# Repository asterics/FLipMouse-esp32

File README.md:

# FLipMouse goes ESP32

This repository contains the ongoing progress on the firmware for the FLipMouse version 3.
It will be API-compatible with FLipMouse v2, but with major improvements on speed (instead of one CortexM0 we will have a dual-core Tensilica and an additional CortexM0 for USB).

If you want to have a look at the FLipMouse v2, follow [this](https://github.com/asterics/FLipMouse) link to the main repository.

The BLE-HID stuff is based on the other [repository](https://github.com/asterics/esp32_mouse_keyboard), where we use the ESP32 as BLE module replacement.

Online demo version of Web GUI: https://asterics.github.io/FLipMouse-esp32/

__Following 3 steps are necessary to completely update/flash the firmware and the necessary support files/devices:__

## Building the ESP32 firmware

Please follow the step-by-step instructions of Espressif's ESP-IDF manual to setup the build infrastructure:
[Setup Toolchain](https://esp-idf.readthedocs.io/en/latest/get-started/index.html#setup-toolchain)

__Note:__ Due to frequent breaking changes within the esp-idf and all build tools, we recommend to use a specific version of the tools:
* release v4.1 (on 04.02.2020)
* master branch (on 04.02.2020)

To get this version, use the following commands:

  `git clone -b release/v4.1 --recursive https://github.com/espressif/esp-idf.git`  
  `cd esp-idf`  
  `./install.sh`  
  `. ./export.sh`  

																																																																																																																																																																																																																																																																																																																																																																																																																																																																																																																																																																																																																																																																																																																																																																																																																																																																																																																																																																																																																																																																																																																																																																																																																																																																																																																																																																																																																																																																																																																																																																																																																																																																																																																																																																																																																																																																																																																																																																																																																																																																																																																																																																																																												
__Now change your directory into the root directory of this repository.__

Create the sdkconfig:
* Execute `make menuconfig` in this directory
* Change: `Serial flasher config` -> `Flash size` to __4MB__
* Change: `Partition table` -> `Partition table` to __Custom partition table CSV__
* Change: `Component config` -> `Bluetooth` to enabled

Optional (for runtime statistics):
* Change: `Component config`->`FreeRTOS`->`Enable FreeRTOS trace facility` to enabled

Optional (extensive stack/heap debugging):
* Change `Component config`->`Heap memory debugging`->`Heap corruption detection` to whatever you need

After a successful setup, you should be able to build the FLipMouse/FABI firmware by executing 'make flash monitor'.

## Building the LPC11U14 firmware (USB bridging chip)

The dedicated USB chip firmware is located in this repository: [usb_bridge](https://github.com/benjaminaigner/usb_bridge/).
Please clone this repository, and import it into the MCUXpresso IDE.

You can download the IDE here:
[MCUXpresso IDE](http://www.nxp.com/mcuxpresso/ide)

After a successful build, you need to flash the firmware to the LPC11U14 chip. We recommend using a development board by Embedded Artists,
because it is very useful for initial testing & debugging. It is possible to split this board into two pieces, one LPC11U14 target and a JTAG
programmer, which we use on a fully assembled FLipMouse. Please refer to the corresponding documents of this board how to connect the JTAG header to
our FLipMouse (will be announced as soon as the PCB is final).

LPCXpresso development board:

[LPCXpresso 11U14](http://embeddedartists.com/products/lpcxpresso/lpc11U14_xpr.php)

## Uploading the WebGUI

The FLipMouse with ESP32 contains a web interface for customizing the parameters. The web page itself is located in the FAT partition as the config data.

-----------------------

TBA: I think it is very easy to use mkfats by copying the component into ESP-IDF and simply call **make mkfatfs** to build the tool and **make flashfatfs** to upload the image.

**BUT** we have a 8.3 naming convention here...

Currently proposed workflow:

-----------------------

Please clone/download the [mkfats](https://github.com/jkearins/ESP32_mkfatfs) tool, and copy the folder `ESP32_mkfatfs/components/mkfatfs` into your
ESP-IDF's components path.

Execute `make mkfatfs` in this repository to build the *mkfatfs* tool.

If you want to update the webpage on the FLipMouse/FABI device, execute:

`make makefatfs flashfatfs`

_WARNING:_** All your slot configuration and IR commands will be deleted by this operation.

## WARNING: THIS IS EARLY WORK IN PROGRESS

# Acknowledgements

Supporters, MA23, people using this device and many more for input.

ESP-IDF developers for HOG testcode

mkfatfs project

thanks to Luca Dentella for the esp32lights demo, see http://www.lucadentella.it/en/2018/01/08/esp32lights/

thanks to Jeroen Domburg and Cornelis for the captive portal DNS code, see: https://github.com/cornelis-61/esp32_Captdns

thanks to Thomas Barth for esp32 Websocket demo code, see https://github.com/ThomasBarth/WebSockets-on-the-ESP32/

thanks to Lucas Bruder for the Neopixel library for ESP32, see https://github.com/Lucas-Bruder/ESP32_LED_STRIP/

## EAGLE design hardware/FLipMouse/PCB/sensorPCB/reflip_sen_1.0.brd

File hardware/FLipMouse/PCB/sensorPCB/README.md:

# Sensor build-up

This sensor carrier is intended to be used with Velostat material. You need a sheet of Velostat, which matches the PCB size (including all holes).

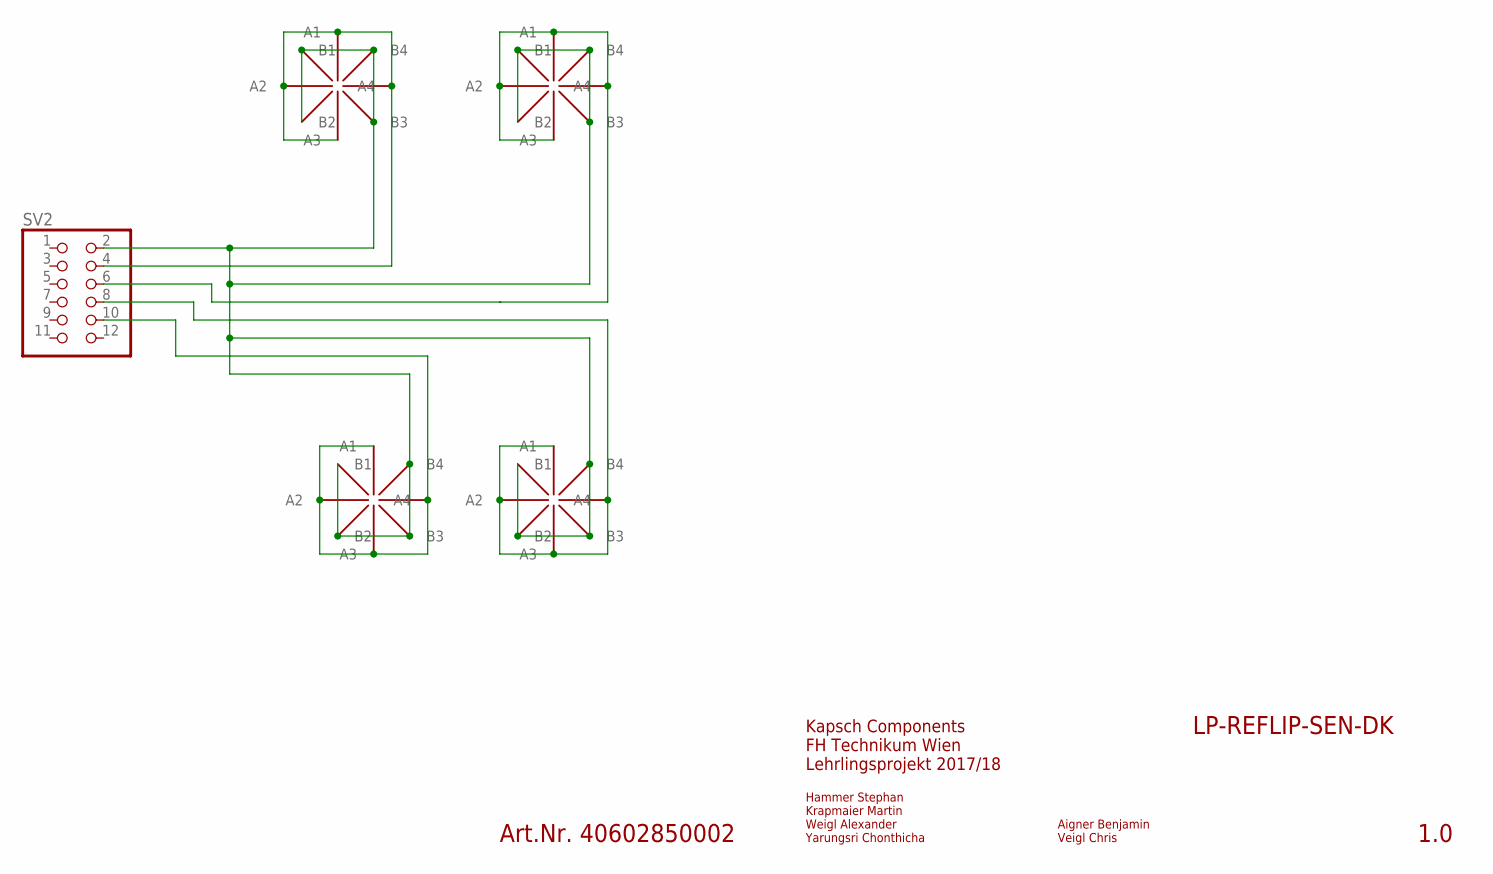
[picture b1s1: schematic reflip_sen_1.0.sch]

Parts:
SV2: PINHD-2X6_2.54-SMD; 2X06SMD
U$1, U$2, U$3, U$4: KONTAKTFLAECHE

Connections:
unnamed: SV2.10, U$2.A1, U$2.A2, U$2.A3, U$2.A4
unnamed: SV2.8, U$4.A1, U$4.A2, U$4.A3, U$4.A4
unnamed: SV2.4, U$1.A1, U$1.A2, U$1.A3, U$1.A4
unnamed: SV2.6, U$3.A1, U$3.A2, U$3.A3, U$3.A4
unnamed: SV2.2, U$1.B1, U$1.B2, U$1.B3, U$1.B4, U$2.B1, U$2.B2, U$2.B3, U$2.B4, U$3.B1, U$3.B2, U$3.B3, U$3.B4, U$4.B1, U$4.B2, U$4.B3, U$4.B4

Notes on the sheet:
Hammer Stephan Krapmaier Martin Weigl Alexander Yarungsri Chonthicha
Kapsch Components FH Technikum Wien Lehrlingsprojekt 2017/18
Art.Nr. 40602850002
Aigner Benjamin Veigl Chris

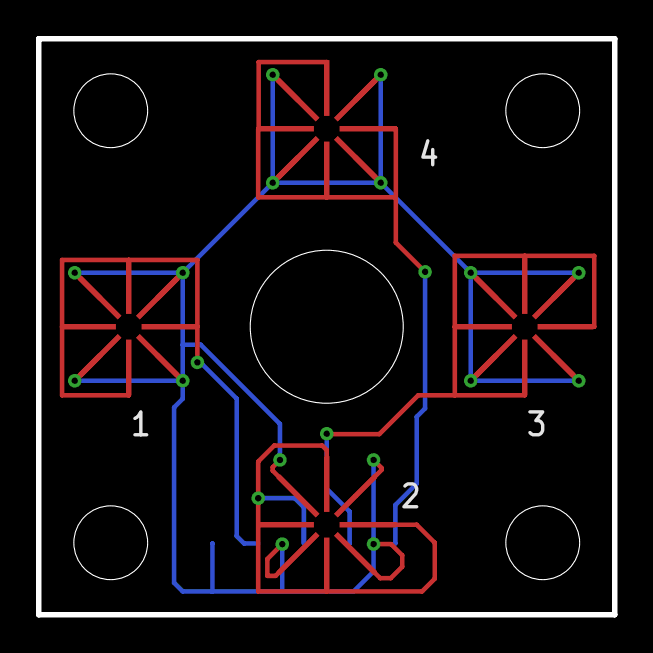
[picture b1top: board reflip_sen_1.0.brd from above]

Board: 2 copper layers, 32.0 x 32.0 mm, 5 parts (1 on the bottom side), 5 nets.

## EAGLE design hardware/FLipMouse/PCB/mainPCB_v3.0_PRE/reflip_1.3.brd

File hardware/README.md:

# FABI

This PCB is intended to be used with a **AK-S-01** case, produced by Szomk.

**Note:** This PCB was not produced yet, so no functional guarantee!

# FLipMouse 

This FLipMouse-esp32 PCB is tested by the *_PRE versions of the PCB.

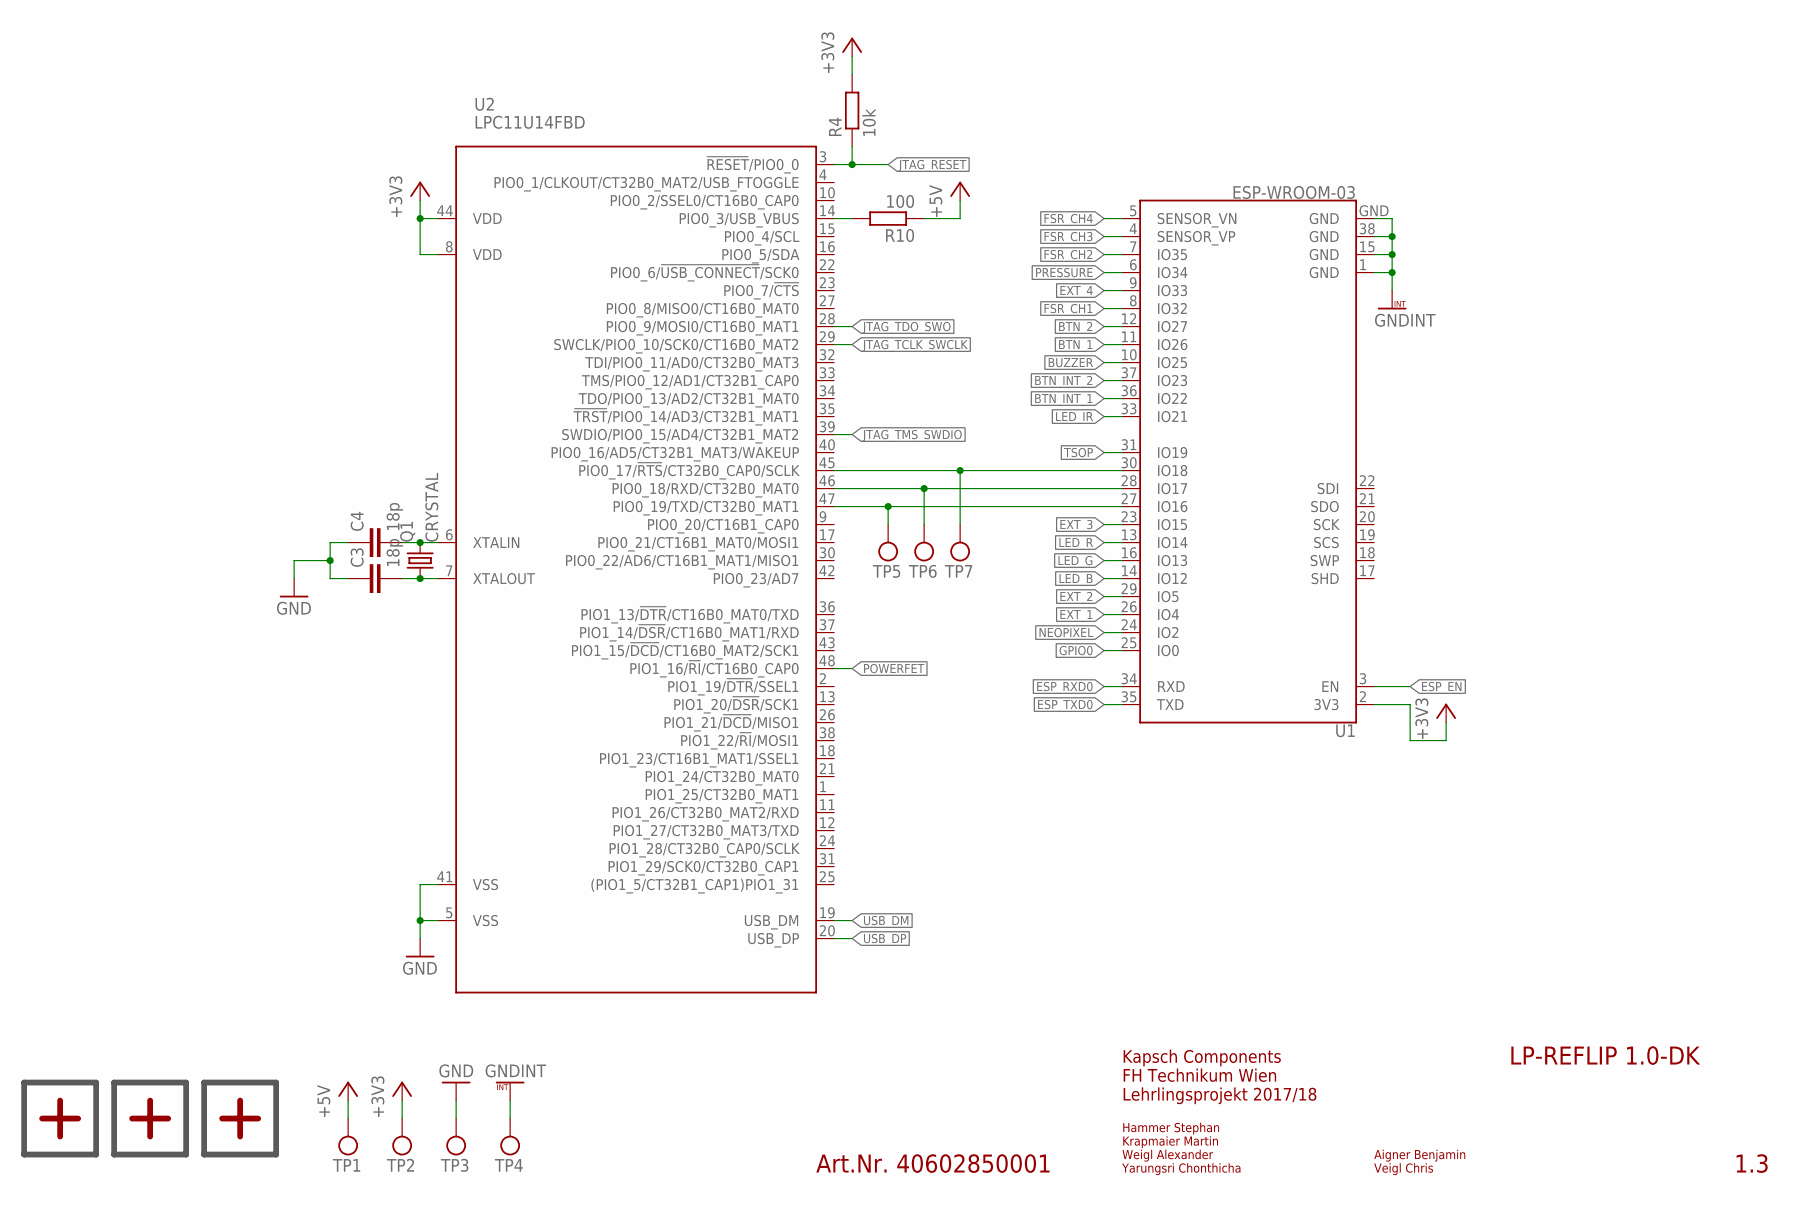
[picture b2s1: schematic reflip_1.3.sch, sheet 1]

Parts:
C3, C4: 18p; C0603
Q1: CRYSTAL
R4: 10k; R0603
R10: 100; R0603
U1: ESP-WROOM-03
U2: LPC11U14FBD; SOT313-2
U$3, U$4, U$5: PASSMARKE
U$6: TP1; TESTPUNKT
U$7: TP2; TESTPUNKT
U$8: TP3; TESTPUNKT
U$9: TP4; TESTPUNKT
U$10: TP7; TESTPUNKT
U$11: TP6; TESTPUNKT
U$12: TP5; TESTPUNKT

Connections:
+3V3: R4.2, U1.2 (3V3), U2.8 (VDD), U2.44 (VDD), U$7.P$1; also elsewhere on the board
+5V: R10.1, U$6.P$1; also elsewhere on the board
BTN_1: U1.11 (IO26); also elsewhere on the board
BTN_2: U1.12 (IO27); also elsewhere on the board
BTN_INT_1: U1.36 (IO22); also elsewhere on the board
BTN_INT_2: U1.37 (IO23); also elsewhere on the board
BUZZER: U1.10 (IO25); also elsewhere on the board
ESP_EN: U1.3 (EN); also elsewhere on the board
ESP_RXD0: U1.34 (RXD); also elsewhere on the board
ESP_TXD0: U1.35 (TXD); also elsewhere on the board
EXT_1: U1.26 (IO4); also elsewhere on the board
EXT_2: U1.29 (IO5); also elsewhere on the board
EXT_3: U1.23 (IO15); also elsewhere on the board
EXT_4: U1.9 (IO33); also elsewhere on the board
FSR_CH1: U1.8 (IO32); also elsewhere on the board
FSR_CH2: U1.7 (IO35); also elsewhere on the board
FSR_CH3: U1.4 (SENSOR_VP); also elsewhere on the board
FSR_CH4: U1.5 (SENSOR_VN); also elsewhere on the board
GND: C3.1, C4.1, U2.5 (VSS), U2.41 (VSS), U$8.P$1; also elsewhere on the board
GNDINT: U1.1 (GND), U1.15 (GND), U1.38 (GND), U1.GND, U$9.P$1; also elsewhere on the board
GPIO0: U1.25 (IO0); also elsewhere on the board
JTAG_RESET: R4.1, U2.3 (!RESET!/PIO0_0); also elsewhere on the board
JTAG_TCLK_SWCLK: U2.29 (SWCLK/PIO0_10/SCK0/CT16B0_MAT2); also elsewhere on the board
JTAG_TDO_SWO: U2.28 (PIO0_9/MOSI0/CT16B0_MAT1); also elsewhere on the board
JTAG_TMS_SWDIO: U2.39 (SWDIO/PIO0_15/AD4/CT32B1_MAT2); also elsewhere on the board
LED_B: U1.14 (IO12); also elsewhere on the board
LED_G: U1.16 (IO13); also elsewhere on the board
LED_IR: U1.33 (IO21); also elsewhere on the board
LED_R: U1.13 (IO14); also elsewhere on the board
LPC_RXD: U1.28 (IO17), U2.46 (PIO0_18/RXD/CT32B0_MAT0), U$11.P$1
LPC_SIG: U1.30 (IO18), U2.45 (PIO0_17/!RTS!/CT32B0_CAP0/SCLK), U$10.P$1
LPC_TXD: U1.27 (IO16), U2.47 (PIO0_19/TXD/CT32B0_MAT1), U$12.P$1
unnamed: C4.2, Q1.P$2 (2), U2.6 (XTALIN)
unnamed: R10.2, U2.14 (PIO0_3/USB_VBUS)
unnamed: C3.2, Q1.P$1 (1), U2.7 (XTALOUT)
NEOPIXEL: U1.24 (IO2); also elsewhere on the board
POWERFET: U2.48 (PIO1_16/!RI!/CT16B0_CAP0); also elsewhere on the board
PRESSURE: U1.6 (IO34); also elsewhere on the board
TSOP: U1.31 (IO19); also elsewhere on the board
USB_DM: U2.19 (USB_DM); also elsewhere on the board
USB_DP: U2.20 (USB_DP); also elsewhere on the board

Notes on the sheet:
Hammer Stephan Krapmaier Martin Weigl Alexander Yarungsri Chonthicha
Kapsch Components FH Technikum Wien Lehrlingsprojekt 2017/18
Aigner Benjamin Veigl Chris
Art.Nr. 40602850001

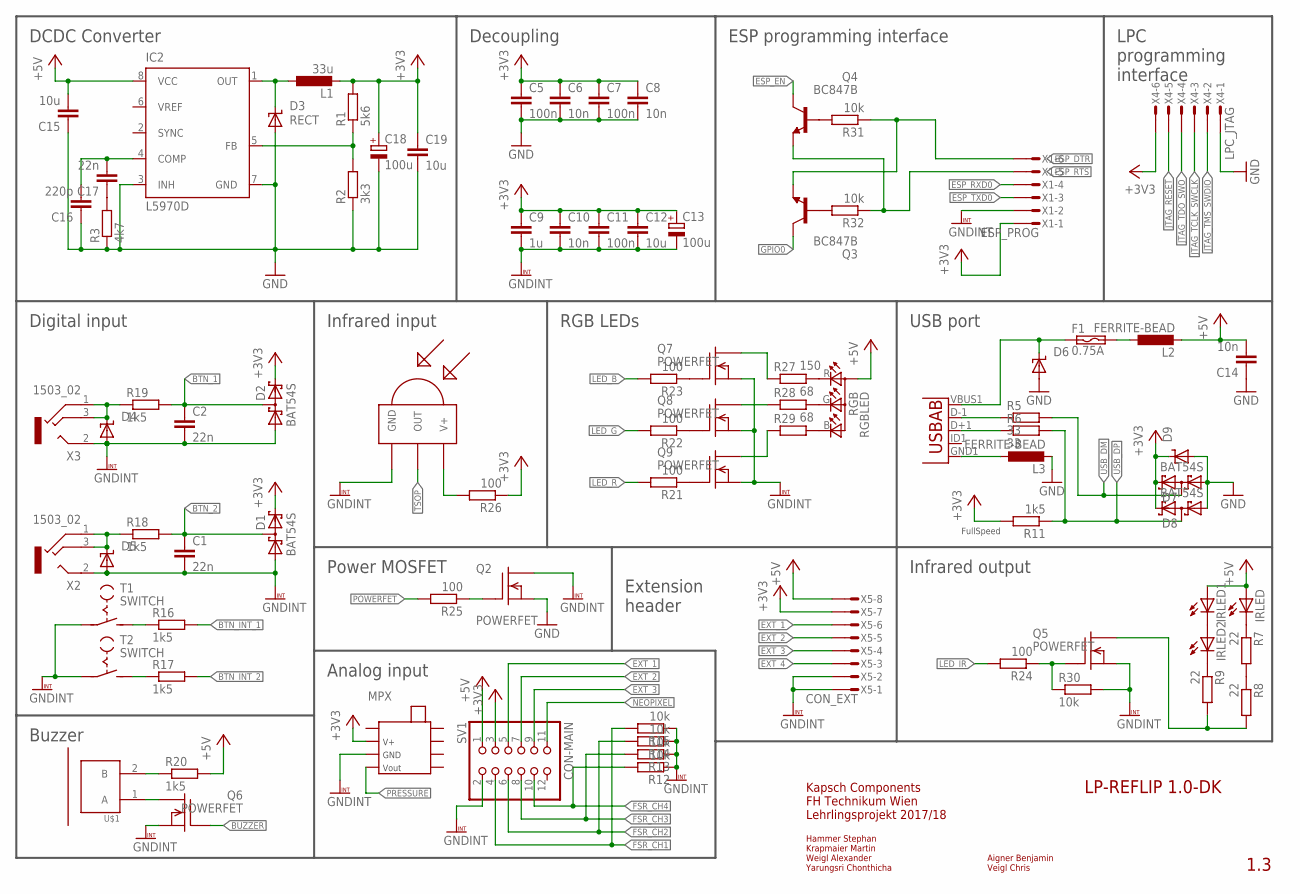
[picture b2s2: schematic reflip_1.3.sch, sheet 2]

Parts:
C1, C2, C17: 22n; C0603
C5, C7, C11: 100n; C0603
C6, C8, C10, C14: 10n; C0603
C9: 1u; C0603
C12, C15, C19: 10u; C0603
C13, C18: 100u; PANASONIC_D
C16: 220p; C0603
D1, D2, D7, D8: BAT54S; SOT23
D3: RECT; SMBJ
D4, D5, D6, D9: TVS-DIODE; SMBJ
F1: 0.75A; FUSE
IC2: L5970D; HSOP8
IRLED, IRLED1, IRLED2: IRLED
L1: 33u; SPULE
L2, L3: FERRITE-BEAD; FERRITEBEAD
MPX: MPX_PRESSURE_SENSOR
Q2, Q5, Q6, Q7, Q8, Q9: POWERFET; SOT-23
Q3, Q4: BC847B; SOT23
R1: 5k6; R0603
R2: 3k3; R0603
R3: 4k7; R0603
R5, R6: 33; R0603
R7, R8, R9: 22; R1206
R11, R16, R17, R18, R19, R20: 1k5; R0603
R12, R13, R14, R15, R30, R31, R32: 10k; R0603
R21, R22, R23, R24, R25, R26: 100; R0603
R27: 150; R0603
R28, R29: 68; R0603
RGB: RGBLED
SV1: CON-MAIN; FE06-2W
T1, T2: SWITCH; SWITCHES
U3: USB""; USB-MICRO-SMD
U$1: PKLCS1212E2400-R1; BUZZ_PIEZO_SMD
U$2: TSOP4838; TSOP18XX
X1: ESP_PROG; MICROMATCH-6SMD
X2, X3: 1503_02
X4: LPC_JTAG; MICROMATCH-6SMD
X5: CON_EXT; MICROMATCH-8-SMD

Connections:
+3V3: C5.1, C6.1, C7.1, C8.1, C9.1, C10.1, C11.1, C12.1, C13.+, C18.+, C19.1, D1.2 (C2), D2.2 (C2), D7.2 (C2), D8.2 (C2), D9.C, L1.P$2 (2), MPX.P$2 (V+), R1.2, R11.2, R26.1, SV1.3, X1.1, X4.6, X5.7; also elsewhere on the board
+5V: C14.2, C15.2, IC2.8 (VCC), IRLED.A, IRLED1.A, L2.P$2 (2), R20.2, RGB.CA (A2), SV1.1, X5.8; also elsewhere on the board
BTN_1: C2.1, D2.3 (C1A2), R19.2; also elsewhere on the board
BTN_2: C1.1, D1.3 (C1A2), R18.2; also elsewhere on the board
BTN_INT_1: R16.2; also elsewhere on the board
BTN_INT_2: R17.2; also elsewhere on the board
BUZZER: Q6.1 (G); also elsewhere on the board
ESP_DTR: Q3.2 (E), R31.1, X1.6
ESP_EN: Q4.3 (C); also elsewhere on the board
ESP_RTS: Q4.2 (E), R32.1, X1.5
ESP_RXD0: X1.4; also elsewhere on the board
ESP_TXD0: X1.3; also elsewhere on the board
EXT_1: SV1.5, X5.6; also elsewhere on the board
EXT_2: SV1.7, X5.5; also elsewhere on the board
EXT_3: SV1.9, X5.4; also elsewhere on the board
EXT_4: X5.3; also elsewhere on the board
FSR_CH1: R15.2, SV1.4; also elsewhere on the board
FSR_CH2: R14.2, SV1.6; also elsewhere on the board
FSR_CH3: R13.2, SV1.8; also elsewhere on the board
FSR_CH4: R12.2, SV1.10; also elsewhere on the board
GND: C5.2, C6.2, C7.2, C8.2, C14.1, C15.1, C16.1, C18.-, C19.2, D3.A, D6.A, D7.1 (A1), D8.1 (A1), D9.A, IC2.3 (INH), IC2.7 (GND), L3.P$2 (2), Q2.2 (S), R2.1, R3.1, X4.1; also elsewhere on the board
GNDINT: C1.2, C2.2, C9.2, C10.2, C11.2, C12.2, C13.-, D1.1 (A1), D2.1 (A1), D4.A, D5.A, MPX.P$3 (GND), Q2.3 (D), Q5.2 (S), Q6.2 (S), Q7.2 (S), Q8.2 (S), Q9.2 (S), R12.1, R13.1, R14.1, R15.1, R30.2, SV1.2, T1.P$3, T2.P$3, U$2.GND, X1.2, X2.2, X3.2, X5.1, X5.2; also elsewhere on the board
GPIO0: Q3.3 (C); also elsewhere on the board
JTAG_RESET: X4.5; also elsewhere on the board
JTAG_TCLK_SWCLK: X4.3; also elsewhere on the board
JTAG_TDO_SWO: X4.4; also elsewhere on the board
JTAG_TMS_SWDIO: X4.2; also elsewhere on the board
LED_B: R23.2; also elsewhere on the board
LED_G: R22.2; also elsewhere on the board
LED_IR: R24.2; also elsewhere on the board
LED_R: R21.2; also elsewhere on the board
unnamed: IC2.5 (FB), R1.1, R2.2
unnamed: Q9.1 (G), R21.1
unnamed: D3.C, IC2.1 (OUT), L1.P$1 (1)
unnamed: R6.1, U3.D+1 (D+)
unnamed: Q2.1 (G), R25.1
unnamed: R5.1, U3.D-1 (D-)
unnamed: C17.1, R3.2
unnamed: IRLED1.C, IRLED2.A
unnamed: C16.2, C17.2, IC2.4 (COMP)
unnamed: Q8.1 (G), R22.1
unnamed: Q7.1 (G), R23.1
unnamed: Q7.3 (D), R27.1
unnamed: IRLED2.C, R9.1
unnamed: R7.2, R8.1
unnamed: R27.2, RGB.R (CRED)
unnamed: D6.C, F1.P$1 (1), U3.VBUS1 (VBUS)
unnamed: F1.P$2 (2), L2.P$1 (1)
unnamed: R17.1, T2.P$4 (S)
unnamed: R20.1, U$1.2 (B)
unnamed: D5.C, R18.1, X2.1, X2.3
unnamed: Q5.3 (D), R8.2, R9.2
unnamed: D4.C, R19.1, X3.1, X3.3
unnamed: Q6.3 (D), U$1.1 (A)
unnamed: R28.2, RGB.G (CGREEN)
unnamed: R26.2, U$2.VCC (V+)
unnamed: L3.P$1 (1), U3.GND1 (GND)
unnamed: R29.2, RGB.B (CBLUE)
unnamed: Q9.3 (D), R29.1
unnamed: Q8.3 (D), R28.1
unnamed: Q5.1 (G), R24.1, R30.1
unnamed: IRLED.C, R7.1
unnamed: Q4.1 (B), R31.2
unnamed: Q3.1 (B), R32.2
NEOPIXEL: SV1.11; also elsewhere on the board
POWERFET: R25.2; also elsewhere on the board
PRESSURE: MPX.P$4 (VOUT); also elsewhere on the board
T1: R16.1, T1.P$4 (S)
TSOP: U$2.OUT; also elsewhere on the board
USB_DM: D7.3 (C1A2), R5.2; also elsewhere on the board
USB_DP: D8.3 (C1A2), R6.2, R11.1; also elsewhere on the board

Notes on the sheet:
DCDC Converter
Decoupling
ESP programming interface
LPC programming interface
Digital input
Infrared input
RGB LEDs
Buzzer
Extension header
Power MOSFET
USB port
Infrared output
FullSpeed
Hammer Stephan Krapmaier Martin Weigl Alexander Yarungsri Chonthicha
Kapsch Components FH Technikum Wien Lehrlingsprojekt 2017/18
Aigner Benjamin Veigl Chris
Analog input

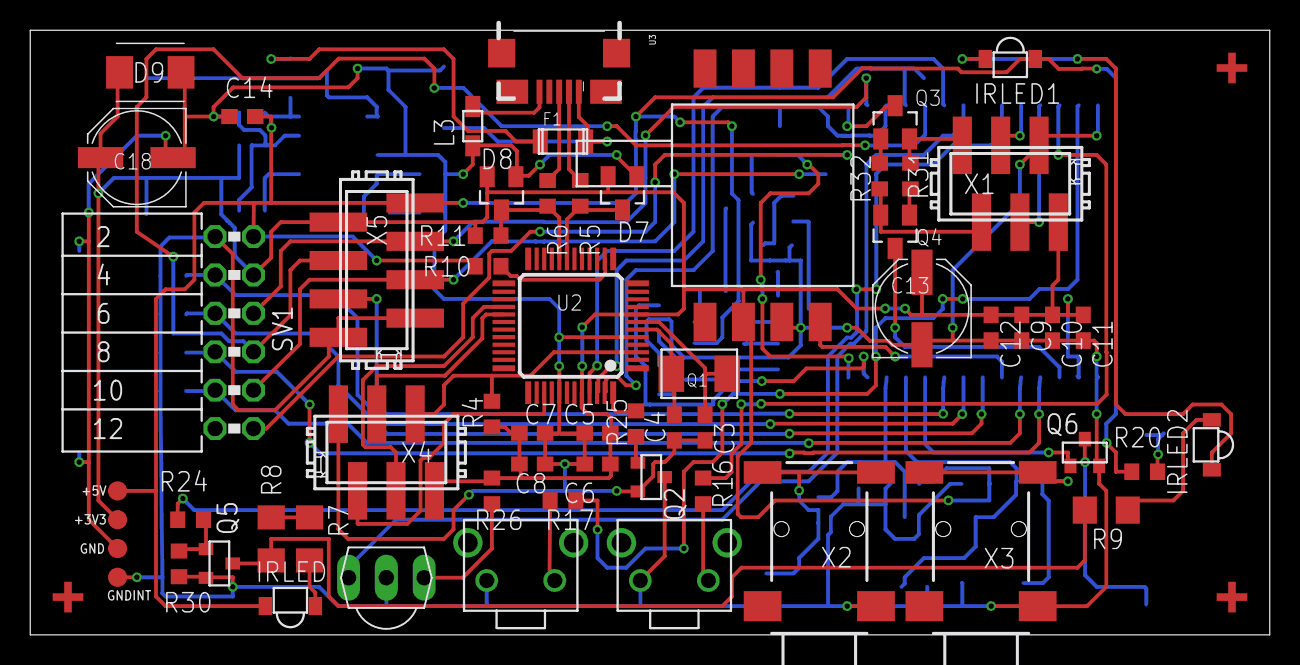
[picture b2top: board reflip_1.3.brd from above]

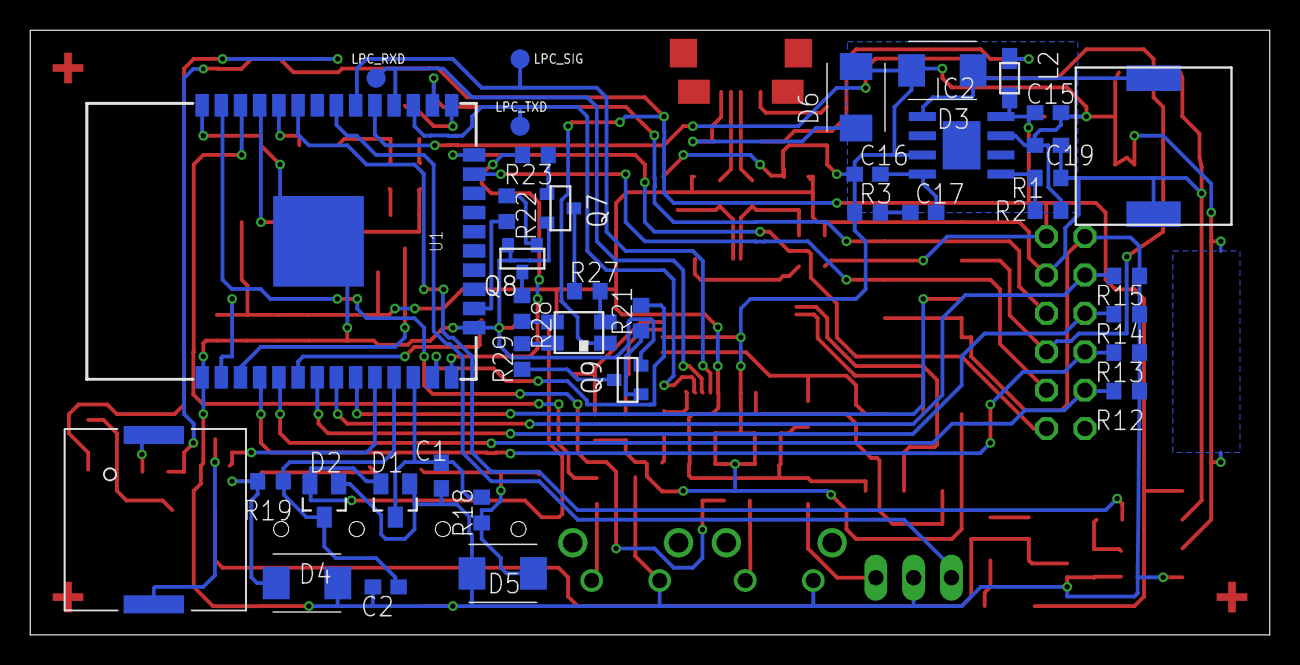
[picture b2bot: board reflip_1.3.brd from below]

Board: 2 copper layers, 82.0 x 40.0 mm, 102 parts (39 on the bottom side), 77 nets.

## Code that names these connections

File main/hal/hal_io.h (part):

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#define HAL_IO_PIN_BUTTON_INT1  5
/** @brief PIN - GPIO pin for internal button 2 (FLipMouse) */
#define HAL_IO_PIN_BUTTON_INT2  14
/** @brief PIN - GPIO pin for buzzer (FLipMouse)
 * @note We will use ledc drivers for the buzzer*/
#define HAL_IO_PIN_BUZZER       25
/** @brief PIN - GPIO pin for IR receiver (TSOP) (FLipMouse) 
 * @note IR will be done with the RMT driver*/
#define HAL_IO_PIN_IR_RECV      12
/** @brief PIN - GPIO pin for IR sender (IR-LED) (FLipMouse)
 * @note IR will be done with the RMT driver */
#define HAL_IO_PIN_IR_SEND      21
/**@brief PIN - GPIO pin for Neopixel onboard LED (&maybe future front LED) */
#define HAL_IO_PIN_NEOPIXEL     22
/** @brief PIN - GPIO pin for external modules */
#define HAL_IO_PIN_EXT          2
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#define HAL_IO_PIN_BUTTON_EXT7  14
/** @brief PIN - GPIO pin for internal button 1 (FABI) */
#define HAL_IO_PIN_BUTTON_INT1  23
/** @brief PIN - GPIO pin for buzzer (FABI)
 * @note We will use ledc drivers for the buzzer*/
#define HAL_IO_PIN_BUZZER       27
/** @brief PIN - GPIO pin for IR receiver (TSOP) (FABI) 
 * @note IR will be done with the RMT driver*/
#define HAL_IO_PIN_IR_RECV      35
/** @brief PIN - GPIO pin for IR sender (IR-LED) (FABI)
 * @note IR will be done with the RMT driver */
#define HAL_IO_PIN_IR_SEND      19
/**@brief PIN - GPIO pin for Neopixel onboard LED */
#define HAL_IO_PIN_NEOPIXEL     22

#endif /* DEVICE_FABI */
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
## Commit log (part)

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2018-05-03 changed colors in order to meet aria contrast criteria
2018-05-03 added translations for "connected" and "not connected"
2018-05-03 added classes for displaying items only for screenreaders and for connection indicators
2018-05-04 changed access keys of sip/puff sliders because alt+e is chrome menu
2018-05-06 Added mode for strong sip/puff
2018-05-06 Added conditions for strong mode + XX in tasks, handling tbd
2018-05-09 Reduced priority of tasks for kbd/mouse/joystick & set baudrate to 115200
2018-05-12 Added a check for current BT status, avoiding errors on re-enabling
2018-05-12 Added compatibility flag
2018-05-12 Starting with slot number 0, not having a "special", not removable slot.
2018-05-12 Added v2.5. note on AT LA/ AT DE
2018-05-12 Put LED update into the macro instead of a task (Neopixel still need a task)
2018-05-16 Fixed heap corruption with reduced buffers
2018-05-21 Changed task priority of config switcher, removed NL characters from ID string
2018-05-21 Added opening partition, to be save if webgui is initialized before storage
2018-05-21 Starting with slot 0, no "DEFAULT" slot
2018-05-21 Changed RMT blocks to 3, on all occasions, freeing one for Neopixels and one for HID output
2018-05-22 Added declaration for queue & usb command
2018-05-23 Added note on slot 0
2018-05-23 Changed for new HID sending
2018-05-23 Added "END" after sending a slot
2018-05-23 Changed storage for slot 0 and -1 for delete all, added note. AT LA bugfix, sending "END" at the end
2018-05-24 Updated documentation & changed loglevel for USB mouse to DEBUG
2018-05-24 Fixed corrupted slots on save due to not-synchronized config data
2018-05-24 Extended data output for saving slots (deactivated by #if 0)
2018-05-28 Removed espressif BLE stuff, added Nkolban's BLE stack
2018-05-28 Improved&simplified calibration:
    - Using same adc read function
    - Removing problem with sensor gain (was not take into account for calibration)
2018-05-28 implemented queue parsing
2018-05-28 BLE/WiFi switch without pairing (is normally active if no device is connected)
2018-05-28 Changed AT BM numbering
2018-05-29 Added sip/puff calibration. Sometimes the 5V type has a significant offset, is calibrated now
2018-05-29 Reduced debug output, controllable via LOG_LEVEL_STORAGE define
2018-05-29 Moved radio switch to main task, reducing stack load on timer
2018-05-29 Reduced main stack size, fixed error on switching off wifi
2018-05-30 Changed stacksize to 8k, replaced printf by ESP_LOGx
2018-05-30 Activated BT/Wifi coexistance, don't know if it helps...
2018-06-04 Changed error checks for getting wifi station count, added guards for wifi deinit
2018-06-04 Doxygen docs updated to current status
2018-06-13 Changed individual tasks to task_hid
2018-06-13 Added HID task
2018-06-13 Added store/load for HID command chain
2018-06-13 Rewrote parser for short HID commands
2018-06-21 Removed now unused kbd/mouse tasks -> moved to task_hid
2018-06-21 Changed comments -> HID task is continous, not functional.
2018-06-21 Changed further to use simple VB task
2018-07-24 Changed sdkconfig & websocket file for esp-idf release v3.1
2018-08-03 Renamed default file to flip.set (allowing a default fabi.set)
2018-08-06 Changed load function to use AT commands from files.
2018-08-07 Major improvements/fixes:
    - Fixed AT AY command
    - Fixing buffer errors on AT SS/AT SP
    - Moved slot storing to an individual function (refactored old printAll function -> now storing AT commands in flash)
    - Slot printing is now mostly done in hal_storage (because the output of "AT LA" is already stored in flash)
2018-08-07 Major improvements:
    - Added a stripping function to remove \r\n
    - Changed config names from 000.fms to 000.set
    - Added serial output to halStorageLoadNumber -> replacing the printAll function from task_commands
    - Added a global file handle for a session, allow appending lines on each call of halStorageStore (less memory for saving AT command lines)
    - Removed all VB/HID chain store/load functions
2018-08-07 Implemented "AT NE" by sending command chain parameter to config switcher queue
2018-08-07 Added breaks for command type detection
2018-08-13 DOXY: Typos, Todos
2018-08-14 OTF calibration, not activated now (missing good values from normal sensors)
2018-10-10 Changed component names for having all part types in one order. Added 3d shapes & beautified silkscreen layers.
2018-10-15 Added requirementsspecification for FABI3 (necessary for certification)
2018-11-15 Production ready, alpha: * Added marks/logos/fiducials * Changed neopixel driving * Moved RX/TX of EXT header from internal UART to free pins * Renumbered all parts for having same part types with fo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
2018-11-21 Checklist: removed EdgeCut layer from single page PCB print Added the update of the 3D renderings
2018-11-21 Improvements&fixes: * Replaced PJ320D (china jack plugs) with plugs from digikey (RoHS!) * Added remaining 3D shapes to PCB * Removed GND from unused jack plug pins (might result in unusable buttons 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
2018-11-25 Pin config update for FABI, removed OTF calibration via defines for FABI
2018-11-25 Added kicad backup files to gitignore, added FABI rescue lib
2018-12-02 Updated FLipMouse PCB: - Routed ADC inputs (FSR+pressure) to LPC11 too (in case of crappy ESP ADC values) - Added ESP32 auto-reset pins to LPC11 (enabling programming via LPC USB) - Cleanup regarding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
2019-01-07 Added function to check if 'sip and puff' is available
2019-01-29 Added default files for FLipMouse configs. Removed gain settings
2019-01-29 Small documentation updates. Fixed R10, according to batch documentation (batch 'a'), from 1k5 to 15R (series resistor for buzzer)
2019-02-05 Clearing empty command queue flag before loading slots. Changed debug level to info
2019-02-05 Changed to use new parser:
    -) Commands are defined now in structure
    -) Parser is based on: https://gitlab.com/ba.1150/cmd_parser_esp32
    -) Parser modifies either the generalConfig_t struct OR calls a handler
2019-02-05 Changed LED number if WiFi is active (now it is purple)
2019-02-05 Added debug output for command chain.
2019-02-05 remove newline
2019-02-06 Keycode parser using parameter, not full string. Added debug output for press action.
2019-02-07 Changed version string to v2.7 (compatible with FlipMouseGUI)
2019-02-08 Updated sdkconfig to esp idf release v3.2
2019-02-08 Changed wifi/ble switching: -) BLE is always active -) BLE/Wifi co-existance is done in esp-idf -) Wifi is switched on/off by the special button handler
2019-02-09 Added detailed debouncer output; added printf macros for printing single bits
2019-02-09 Replaced the out event flags (signalling to task_hid, task_vb) by an event loop:
    -) renamed task_hid / task_vb to handler_hid/handler_vb
    -) Deleted virtualButtonsOut event group
    -) Removed task structure, replaced by event handler
    -) Changed functions in all calling modules
2019-02-12 Fixed wrong IR file numbering -> could play, delete but not storing more than one IR command.
2019-02-13 Debouncer has highest priority.
2019-02-13 Fixed AT K* commands: press/release flags were wrong Cleaned up deboug output
2019-02-13 Fixed wrong press/release assignment for keyboard actions; removed trailing \r\n characters
2019-02-13 Fixed check for slot number (do this only on creating a new slot)
2019-03-08 Small comment updates; changed default slot settings
2019-03-11 ADC measurements via LPC - I2C communication for data
2019-03-11 Unified 3V3 (switched), according to chapter 9.4 of LPC datasheet, the high power pin doesn't deliver 3v3.
2019-03-13 Added an output for parsing errors.
2019-03-13 Changed log output to level info
2019-03-13 Changed SPIFFS script, modified sdkconfig to use same SPIFFS settings as mkspiffs in standard configuration
2019-03-15 UPdates in tone creation, queue was too short for e.g. slot nr 5 beeps.
2019-03-15 Disabled elliptic deadzone, can be enabled by define
2019-03-15 Fixed missing X+Y axis mouse command (was only active for a single axis).
2019-03-18 Moved BLE/Wifi init to the end with a delay
2019-03-20 Doxygen updates, resetting mouse wheel size to 3 if not set.
2019-03-22 Masked out press/release flag for getting active VBs
2019-03-22 Implemented strong sip/puff + additional action, cleaned up ADC code, removed ESP32's ADC init (unused)
2019-03-22 Doxygen - pulled to current source
2019-04-02 Updated PCB, final changes & refinements for v3.1b
2019-05-28 Improved error handling on spurious unusable sensor readings
2019-05-28 Improved web server handling:
    -) Tasks are correctly deleted after wifi disable
    -) Wifi can be enabled only once each power cycle
2019-07-04 Fixed restore defaults in webgui, done via "AT DE" followed by "AT LA"
2019-07-04 Added a partition table for OTA setup, see: https://github.com/asterics/esp32-uart-ota
2019-07-04 Updated doxygen docs
2019-07-10 Finalized MQTT. Working now in station mode, possible to add it on a VB
2019-07-10 added numbering details in hal_storage get slot number, fixed color error when wifi softap is deactivated
2019-07-11 Temporary commit, not buildable
2019-07-11 Added AT MQ & AT RE (MQTT & REST calls) as possible button actions to webgui
2019-07-17 made menubutton display flex -> everytime same height; added new tab "global config"
2019-07-18 added possibility to pass style to createElement
2019-07-18 added ID to spacer to be able to show/hide in javascript
2019-07-18 added possibility to define maximum timeout to resolve, if no result was received
2019-07-18 filled global properties tab
2019-07-18 changed AT IL lineending to \r\n
2019-07-19 Documented LED color on Wifi SoftAP activation
2019-07-19 Modified Websocket helper to support 16bits & 64bits payload length fields. UNTESTED
2019-07-19 Added output of general settings (AT MH, AT WH, AT ML)
2019-07-19 added node_modules to gitignore
2019-07-19 Added note on http URL length, added cleanup and check for active SoftAP wifi
2019-07-22 updated FABI webgui with changes from FlipMouse, harmonized code structure in tabact.js
2019-07-22 remember inital result of "isSipAndPuffLive" and reuse it
2019-07-22 added minified and gzipped versions of FABI and FLipmouse sources
2019-07-31 Added script for auto-generating a new webGUI image (SPIFFS)
2019-11-09 Working serial port interface, hardcoded USB IF!
2019-11-12 Fixed memory leak (with many action handlers in promise), fixed the wind-up of concat return data.
2019-12-05 With promises for port open
2019-12-06 Added the correct value handlers
2020-02-04 Updates for newer esp-idf (release v4 or todays master): -) removed unused variable of hal_ble -) changed wifi_get_reason to esp_err_to_name -) Added a guard macro for task statistics -) Changed base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
2020-03-23 Closing serial port if not successful, fixed a typo
2020-03-23 Added sloat loading, depending on running processes/apps/programs:
    The FLipMouseGUI can run now in the tray, supporting a slot switch
    depending on the running programs.
    For this function, the tab "Slots" has the possibility to set
    a program (from the list of currently running programs) for
    each slot.
    Note: these settings are NOT stored on the FLipMouse, but in a JSON
2020-03-25 Added IR tab to HTML
2020-03-26 Changed delete all IR command to constant
2020-04-05 added some details about toolchain to Readme
2020-07-07 Bump electron from 5.0.12 to 7.2.4 in /webgui/src/fabi
    Bumps [electron](https://github.com/electron/electron) from 5.0.12 to 7.2.4.
    - [Release notes](https://github.com/electron/electron/releases)
    - [Changelog](https://github.com/electron/electron/blob/master/docs/breaking-changes.md)
    - [Commits](https://github.com/electron/electron/compare/v5.0.12...v7.2.4)
2020-07-26 Bump lodash from 4.17.15 to 4.17.19 in /webgui/src/flipmouse
    Bumps [lodash](https://github.com/lodash/lodash) from 4.17.15 to 4.17.19.
    - [Release notes](https://github.com/lodash/lodash/releases)
    - [Commits](https://github.com/lodash/lodash/compare/4.17.15...4.17.19)
2020-09-02 Bump bl from 3.0.0 to 3.0.1 in /webgui/src/fabi
    Bumps [bl](https://github.com/rvagg/bl) from 3.0.0 to 3.0.1.
    - [Release notes](https://github.com/rvagg/bl/releases)
    - [Commits](https://github.com/rvagg/bl/compare/v3.0.0...v3.0.1)
2020-10-28 Added version parser for local/available FM version, added tycmd update command.
2020-12-12 Bump ini from 1.3.5 to 1.3.8 in /webgui/src/fabi
    Bumps [ini](https://github.com/isaacs/ini) from 1.3.5 to 1.3.8.
    - [Release notes](https://github.com/isaacs/ini/releases)
    - [Commits](https://github.com/isaacs/ini/compare/v1.3.5...v1.3.8)
2021-01-13 Added download&upload of slot text files

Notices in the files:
main/hal/hal_io.h:
This program is free software; you can redistribute it and/or modify
it under the terms of the GNU General Public License as published by
the Free Software Foundation; either version 2 of the License, or
(at your option) any later version.
Copyright 2017 Benjamin Aigner <aignerb@technikum-wien.at,
beni@asterics-foundation.org>
